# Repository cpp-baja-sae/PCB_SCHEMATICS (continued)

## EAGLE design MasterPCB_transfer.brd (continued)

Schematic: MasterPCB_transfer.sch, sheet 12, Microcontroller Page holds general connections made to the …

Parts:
40G_GPIO: SMALL_TP
!CS_ADC: SMALL_TP
!IMU_CS: SMALL_TP
!IMU_RST: SMALL_TP
!ISO_CS: SMALL_TP
!TEMP_CS: SMALL_TP
BUSY_ADC_1, BUSY_ADC_2, BUSY_ADC_3: SMALL_TP
CD/DAT3_SPI-CS: SMALL_TP
CLK: SMALL_TP
CMD_SPI-DI: SMALL_TP
CONVAB_ADC: SMALL_TP
DAT1, DAT2: SMALL_TP
DAT_SPI-DO: SMALL_TP
DIN1, DIN2, DIN3, DIN4, DIN5, DIN6, DIN7, DIN8: SMALL_TP
DOUTA_ADC_1, DOUTA_ADC_2, DOUTA_ADC_3: SMALL_TP
DOUTB_ADC_1, DOUTB_ADC_2, DOUTB_ADC_3: SMALL_TP
FSTD_ADC_1, FSTD_ADC_2, FSTD_ADC_3: SMALL_TP
GPS_EN: SMALL_TP
GPS_RX: SMALL_TP
GPS_TX: SMALL_TP
IMU_DIN: SMALL_TP
IMU_DOUT: SMALL_TP
IMU_DR: SMALL_TP
IMU_SCLK: SMALL_TP
IMU_SYNC: SMALL_TP
ISO_MISO: SMALL_TP
ISO_MOSI: SMALL_TP
ISO_SPI_CH_SEL: SMALL_TP
ISO_SPI_HZ_SW: SMALL_TP
ISO_SPI_SCLK: SMALL_TP
ISO_SPI_SLOW: SMALL_TP
J4, J12, J14: TFM-140-02-L-D-WT-K; SAMTEC_TFM-140-02-L-D-WT-K
LED_1, LED_2, LED_3: SMALL_TP
LED_P: SMALL_TP
MASS_ON: SMALL_TP
OS0_ADC, OS1_ADC, OS2_ADC: SMALL_TP
PA0, PA3, PA4, PA5, PA6, PA8, PA9, PA10, PA11, PA12, PA13, PA14, PA15: SMALL_TP
PB0, PB1, PB2, PB3, PB4, PB5, PB6, PB7, PB8, PB9, PB10, PB11, PB12, PB14, PB15: SMALL_TP
PC0, PC2, PC3, PC6, PC7, PC8, PC9, PC10, PC11, PC12, PC13: SMALL_TP
PD0, PD1, PD2, PD3, PD4, PD5, PD6, PD7, PD11, PD12, PD13, PD14, PD15: SMALL_TP
PE0, PE1, PE2, PE3, PE4, PE5, PE6, PE7, PE8, PE9, PE10, PE11, PE12, PE13, PE14, PE15: SMALL_TP
PF0, PF1, PF2, PF3, PF4, PF5, PF6, PF7, PF8, PF9, PF10, PF11, PF12, PF13, PF14, PF15: SMALL_TP
PG0, PG1, PG2, PG3, PG4, PG5, PG6, PG8, PG9, PG10, PG12, PG14, PG15: SMALL_TP
PH1: SMALL_TP
P_FAULT1, P_FAULT2, P_FAULT3: SMALL_TP
RST_ADC: SMALL_TP
SCL1, SCL2: SMALL_TP
SCLK_ADC: SMALL_TP
SDA1, SDA2: SMALL_TP
TEMP_MISO: SMALL_TP
TEMP_SCLK: SMALL_TP
U$5, U$7, U$9, U$10, U$14, U$15: THROUGH_HOLE; 1/16TH_BOLT
UC1: NUCLEO_H723ZG

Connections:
3.3V_MCU: UC1.3V3_VDD
3.3V_SWITCHING: J12.28, J12.30, J12.32, J12.34, J12.36, J12.38; also elsewhere on the board
5V_CONNECTOR: J12.16, J12.18, J12.20, J12.22, J12.24, J12.26; also elsewhere on the board
5V_MCU: UC1.5V_EXT; also elsewhere on the board
13.5V_BUS: J12.02, J12.04, J12.06, J12.08, J12.10, J12.12, J12.14; also elsewhere on the board
40G_GPIO: 40G_GPIO.TP, J4.40; also elsewhere on the board
!CS_ADC: !CS_ADC.TP, J4.53; also elsewhere on the board
!IMU_CS: !IMU_CS.TP, J4.03; also elsewhere on the board
!IMU_RST: !IMU_RST.TP, J4.01; also elsewhere on the board
!ISO_CS: !ISO_CS.TP, J4.28; also elsewhere on the board
!THERMOCOUPLE_CS: !TEMP_CS.TP, J4.36; also elsewhere on the board
BUSY_ADC_1: BUSY_ADC_1.TP, J4.55; also elsewhere on the board
BUSY_ADC_2: BUSY_ADC_2.TP, J4.63; also elsewhere on the board
BUSY_ADC_3: BUSY_ADC_3.TP, J4.71; also elsewhere on the board
CONVSTAB_ADC: CONVAB_ADC.TP, J4.47; also elsewhere on the board
DOUTA_ADC_1: DOUTA_ADC_1.TP, J4.61; also elsewhere on the board
DOUTA_ADC_2: DOUTA_ADC_2.TP, J4.69; also elsewhere on the board
DOUTA_ADC_3: DOUTA_ADC_3.TP, J4.77; also elsewhere on the board
DOUTB_ADC_1: DOUTB_ADC_1.TP, J4.59; also elsewhere on the board
DOUTB_ADC_2: DOUTB_ADC_2.TP, J4.67; also elsewhere on the board
DOUTB_ADC_3: DOUTB_ADC_3.TP, J4.75; also elsewhere on the board
D_SENSE1: DIN1.TP, J4.66; also elsewhere on the board
D_SENSE2: DIN2.TP, J4.68; also elsewhere on the board
D_SENSE3: DIN3.TP, J4.70; also elsewhere on the board
D_SENSE4: DIN4.TP, J4.72; also elsewhere on the board
D_SENSE5: DIN5.TP, J4.74; also elsewhere on the board
D_SENSE6: DIN6.TP, J4.76; also elsewhere on the board
D_SENSE7: DIN7.TP, J4.78; also elsewhere on the board
D_SENSE8: DIN8.TP, J4.80; also elsewhere on the board
ETH_CRS_DV: UC1.PA7
ETH_MDC: UC1.PC1
ETH_MDIO: UC1.PA2
ETH_REF_CLK: UC1.PA1
ETH_RXD0: UC1.PC4
ETH_RXD1: UC1.PC5
ETH_TXD0: UC1.PG13
ETH_TXD1: UC1.PB13
ETH_TX_EN: UC1.PG11
FIRSTDATA_ADC_1: FSTD_ADC_1.TP, J4.57; also elsewhere on the board
FIRSTDATA_ADC_2: FSTD_ADC_2.TP, J4.65; also elsewhere on the board
FIRSTDATA_ADC_3: FSTD_ADC_3.TP, J4.73; also elsewhere on the board
FLASH_CD/DAT3_SPI-CS: CD/DAT3_SPI-CS.TP, J4.08; also elsewhere on the board
FLASH_CLK: CLK.TP, J4.12; also elsewhere on the board
FLASH_CMD_SPI-DI: CMD_SPI-DI.TP, J4.10; also elsewhere on the board
FLASH_DAT0_SPI-DO: DAT_SPI-DO.TP, J4.02; also elsewhere on the board
FLASH_DAT1: DAT1.TP, J4.04; also elsewhere on the board
FLASH_DAT2: DAT2.TP, J4.06; also elsewhere on the board
GND: J12.39, J12.40, J12.41, J12.42, J12.43, J12.44, J12.45, J12.46, J12.47, J12.48, J12.49, J12.50, J12.51, J12.52, J12.53, J12.54, J12.55, J12.56, J12.57, J12.58, J12.59, J12.60, J12.61, J12.62, J12.63, J12.64, J12.65, J12.66, J12.67, J12.68, J12.69, J12.70, J12.71, J12.72, J12.73, J12.74, J12.75, J12.76, J12.77, J12.78, J12.79, J12.80, UC1.10 (GND), UC1.19 (GND), UC1.40 (GND), UC1.53 (GND), UC1.64 (GND), UC1.71 (GND), UC1.72 (GND), UC1.79 (GND), UC1.91 (GND), UC1.92 (GND), UC1.93 (GND), UC1.122 (GND), UC1.131 (GND), UC1.143 (GND), UC1.144 (GND); also elsewhere on the board
GPS_EN: GPS_EN.TP, J4.39; also elsewhere on the board
GPS_RX: GPS_RX.TP, J4.37; also elsewhere on the board
GPS_TX: GPS_TX.TP, J4.35; also elsewhere on the board
IMU_DIN: IMU_DIN.TP, J4.05; also elsewhere on the board
IMU_DOUT: IMU_DOUT.TP, J4.07; also elsewhere on the board
IMU_DR: IMU_DR.TP, J4.13; also elsewhere on the board
IMU_SCLK: IMU_SCLK.TP, J4.09; also elsewhere on the board
IMU_SYNC: IMU_SYNC.TP, J4.11; also elsewhere on the board
ISO_MISO: ISO_MISO.TP, J4.26; also elsewhere on the board
ISO_MOSI: ISO_MOSI.TP, J4.24; also elsewhere on the board
ISO_SPI_CH_SEL: ISO_SPI_CH_SEL.TP, J4.18; also elsewhere on the board
ISO_SPI_HIGH_Z_SWITCH: ISO_SPI_HZ_SW.TP, J4.20; also elsewhere on the board
ISO_SPI_SCLK: ISO_SPI_SCLK.TP, J4.22; also elsewhere on the board
ISO_SPI_SLOW: ISO_SPI_SLOW.TP, J4.30; also elsewhere on the board
LED_OUT1: J4.62, LED_1.TP; also elsewhere on the board
LED_OUT2: J4.60, LED_2.TP; also elsewhere on the board
LED_OUT3: J4.58, LED_3.TP; also elsewhere on the board
MASS_ON: J4.25, MASS_ON.TP; also elsewhere on the board
OS0_ADC: J4.41, OS0_ADC.TP; also elsewhere on the board
OS1_ADC: J4.43, OS1_ADC.TP; also elsewhere on the board
OS2_ADC: J4.45, OS2_ADC.TP; also elsewhere on the board
PA0: J14.01, PA0.TP, UC1.PA0
PA3: J14.03, PA3.TP, UC1.PA3
PA4: J14.05, PA4.TP, UC1.PA4
PA5: J14.07, PA5.TP, UC1.PA5
PA6: J14.09, PA6.TP, UC1.PA6
PA8: J14.11, PA8.TP, UC1.PA8
PA9: J14.13, PA9.TP, UC1.PA9
PA10: J14.15, PA10.TP, UC1.PA10
PA11: J14.17, PA11.TP, UC1.PA11
PA12: J14.19, PA12.TP, UC1.PA12
PA13: J14.21, PA13.TP, UC1.PA13
PA14: J14.23, PA14.TP, UC1.PA14
PA15: J14.25, PA15.TP, UC1.PA15
PB0: J14.27, PB0.TP, UC1.PB0
PB1: J14.29, PB1.TP, UC1.PB1
PB2: J14.31, PB2.TP, UC1.PB2
PB3: J14.33, PB3.TP, UC1.PB3
PB4: J14.35, PB4.TP, UC1.PB4
PB5: J14.37, PB5.TP, UC1.PB5
PB6: J14.39, PB6.TP, UC1.PB6
PB7: J14.79, PB7.TP, UC1.PB7
PB8: J14.77, PB8.TP, UC1.PB8
PB9: J14.75, PB9.TP, UC1.PB9
PB10: J14.73, PB10.TP, UC1.PB10
PB11: J14.71, PB11.TP, UC1.PB11
PB12: J14.69, PB12.TP, UC1.PB12
PB14: J14.65, PB14.TP, UC1.PB14
PB15: J14.63, PB15.TP, UC1.PB15
PC0: J14.61, PC0.TP, UC1.PC0
PC2: J14.59, PC2.TP, UC1.PC2
PC3: J14.57, PC3.TP, UC1.PC3
PC6: J14.55, PC6.TP, UC1.PC6
PC7: J14.53, PC7.TP, UC1.PC7
PC8: J14.51, PC8.TP, UC1.PC8
PC9: J14.49, PC9.TP, UC1.PC9
PC10: J14.47, PC10.TP, UC1.PC10
PC11: J14.45, PC11.TP, UC1.PC11
PC12: J14.43, PC12.TP, UC1.PC12
PC13: J14.41, PC13.TP, UC1.PC13
PC14-0SC32_IN: UC1.PC14
PC15-OSC32_OUT: UC1.PC15
PD0: J14.02, PD0.TP, UC1.PD0
PD1: J14.04, PD1.TP, UC1.PD1
PD2: J14.06, PD2.TP, UC1.PD2
PD3: J14.08, PD3.TP, UC1.PD3
PD4: J14.10, PD4.TP, UC1.PD4
PD5: J14.12, PD5.TP, UC1.PD5
PD6: J14.14, PD6.TP, UC1.PD6
PD7: J14.16, PD7.TP, UC1.PD7
PD11: J14.18, PD11.TP, UC1.PD11
PD12: J14.20, PD12.TP, UC1.PD12
PD13: J14.22, PD13.TP, UC1.PD13
PD14: J14.24, PD14.TP, UC1.PD14
PD15: J14.26, PD15.TP, UC1.PD15
PE0: J14.28, PE0.TP, UC1.PE0
PE1: J14.30, PE1.TP, UC1.PE1
PE2: J14.32, PE2.TP, UC1.PE2
PE3: J14.34, PE3.TP, UC1.PE3
PE4: J14.36, PE4.TP, UC1.PE4
PE5: J14.38, PE5.TP, UC1.PE5
PE6: J14.40, PE6.TP, UC1.PE6
PE7: J14.80, PE7.TP, UC1.PE7
PE8: J14.78, PE8.TP, UC1.PE8
PE9: J14.76, PE9.TP, UC1.PE9
PE10: J14.74, PE10.TP, UC1.PE10
PE11: J14.72, PE11.TP, UC1.PE11
PE12: J14.70, PE12.TP, UC1.PE12
PE13: J14.68, PE13.TP, UC1.PE13
PE14: J14.66, PE14.TP, UC1.PE14
PE15: J14.64, PE15.TP, UC1.PE15
PF0: J12.23, PF0.TP, UC1.PF0
PF1: J14.62, PF1.TP, UC1.PF1
PF2: J14.60, PF2.TP, UC1.PF2
PF3: J14.58, PF3.TP, UC1.PF3
PF4: J14.56, PF4.TP, UC1.PF4
PF5: J14.54, PF5.TP, UC1.PF5
PF6: J14.52, PF6.TP, UC1.PF6
PF7: J14.50, PF7.TP, UC1.PF7
PF8: J14.48, PF8.TP, UC1.PF8
PF9: J14.46, PF9.TP, UC1.PF9
PF10: J14.44, PF10.TP, UC1.PF10
PF11: J14.42, PF11.TP, UC1.PF11
PF12: J12.01, PF12.TP, UC1.PF12
PF13: J12.03, PF13.TP, UC1.PF13
PF14: J12.05, PF14.TP, UC1.PF14
PF15: J12.07, PF15.TP, UC1.PF15
PG0: J12.09, PG0.TP, UC1.PG0
PG1: J12.11, PG1.TP, UC1.PG1
PG2: J12.13, PG2.TP, UC1.PG2
PG3: J12.15, PG3.TP, UC1.PG3
PG4: J12.17, PG4.TP, UC1.PG4
PG5: J12.19, PG5.TP, UC1.PG5
PG6: J12.21, PG6.TP, UC1.PG6
PG8: J12.25, PG8.TP, UC1.PG8
PG9: J12.27, PG9.TP, UC1.PG9
PG10: J12.29, PG10.TP, UC1.PG10
PG12: J12.31, PG12.TP, UC1.PG12
PG14: J12.33, PG14.TP, UC1.PG14
PG15: J12.35, PG15.TP, UC1.PG15
PH0-OSC_IN: UC1.PH0
PH1: J12.37, PH1.TP, UC1.PH1
POWER_FAULT1: J4.15, P_FAULT1.TP; also elsewhere on the board
POWER_FAULT2: J4.17, P_FAULT2.TP; also elsewhere on the board
POWER_FAULT3: J4.19, P_FAULT3.TP; also elsewhere on the board
P_LED: J4.64, LED_P.TP; also elsewhere on the board
RESET_ADC: J4.49, RST_ADC.TP; also elsewhere on the board
SCL1: J4.23, SCL1.TP; also elsewhere on the board
SCL2: J4.29, SCL2.TP; also elsewhere on the board
SCLK_ADC: J4.51, SCLK_ADC.TP; also elsewhere on the board
SDA1: J4.21, SDA1.TP; also elsewhere on the board
SDA2: J4.27, SDA2.TP; also elsewhere on the board
THERMOCOUPLE_MISO: J4.34, TEMP_MISO.TP; also elsewhere on the board
THERMOCOUPLE_SCLK: J4.32, TEMP_SCLK.TP; also elsewhere on the board
USART3_TX: UC1.PD8
USART4_RX: UC1.PD9
USB_FS_OVCR: UC1.PG7
USB_FS_PWR_EN: UC1.PD10

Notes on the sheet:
Pins labeled DNC _ # are pins connected for hardware on board
RED LED - There is an issue YELLOW LED - Digital coms GREEN LED - Power Good BLUE LED - Power at location is available
Board LED indicators
Microcontroller pin breakout connector Expose all non-static set pins for easy access and to enable swapping pin configurations as well
All digital connections go through connector Enables easy flexibility to rewire any digital system on demand
Flash interface
ISO SPI link interface
Back up thermocouple spi link interface
Digital input
Driver indicators
GPS interface
IMU interface
Power fault input
E-Fuse interface
ADC interface

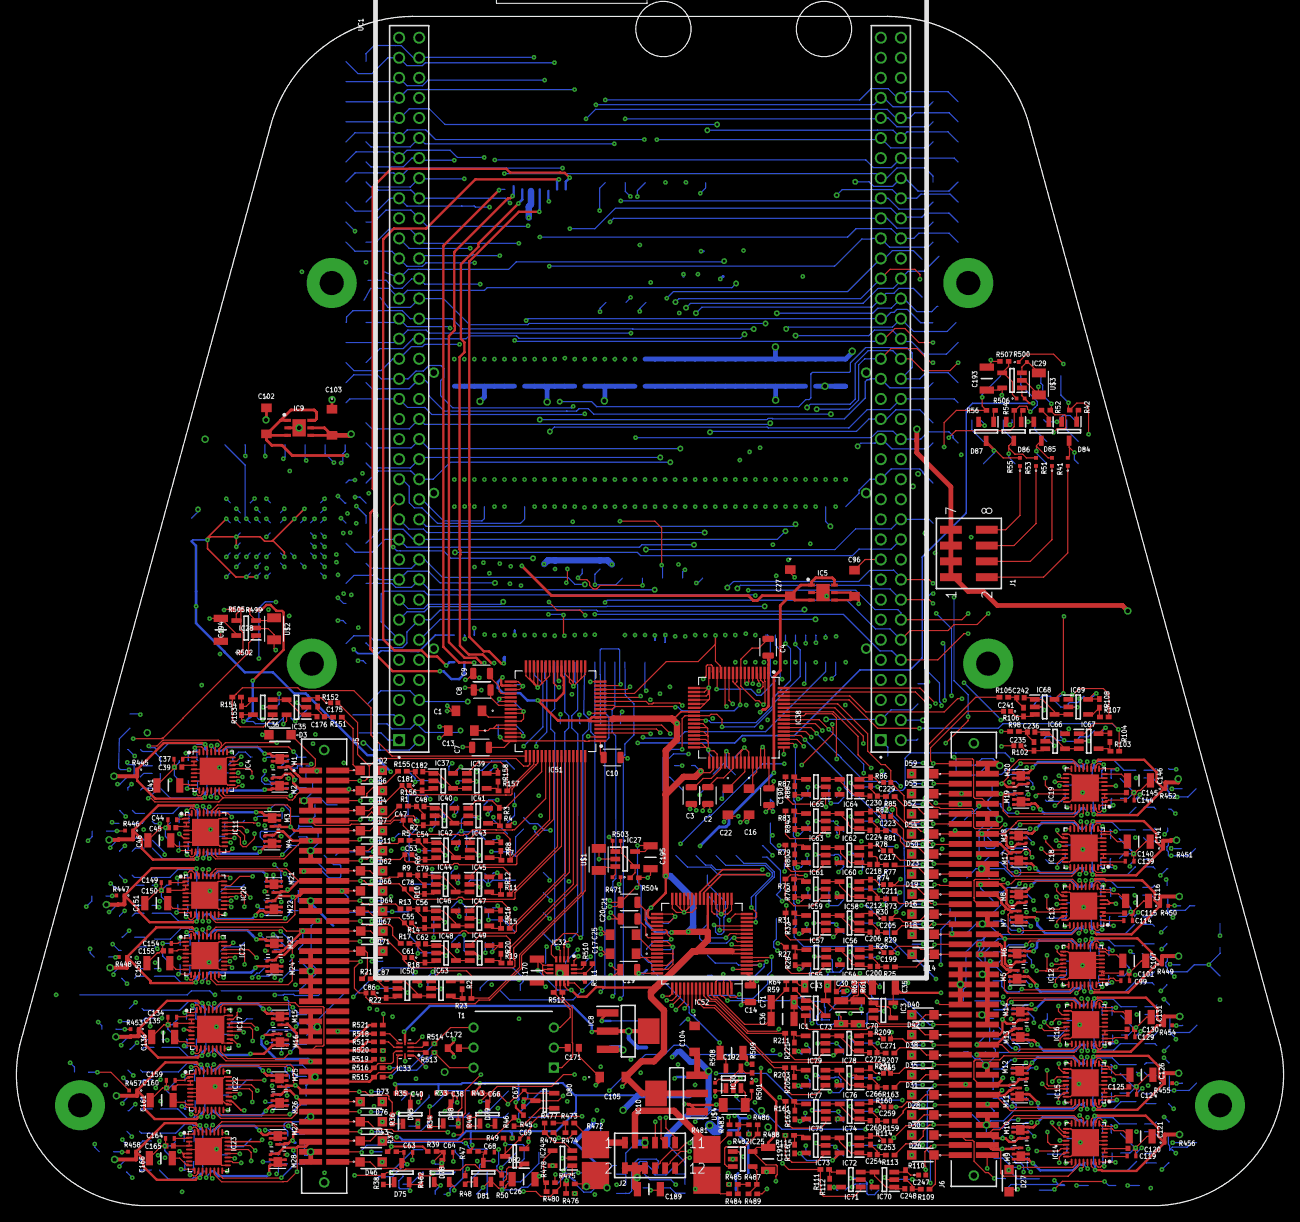
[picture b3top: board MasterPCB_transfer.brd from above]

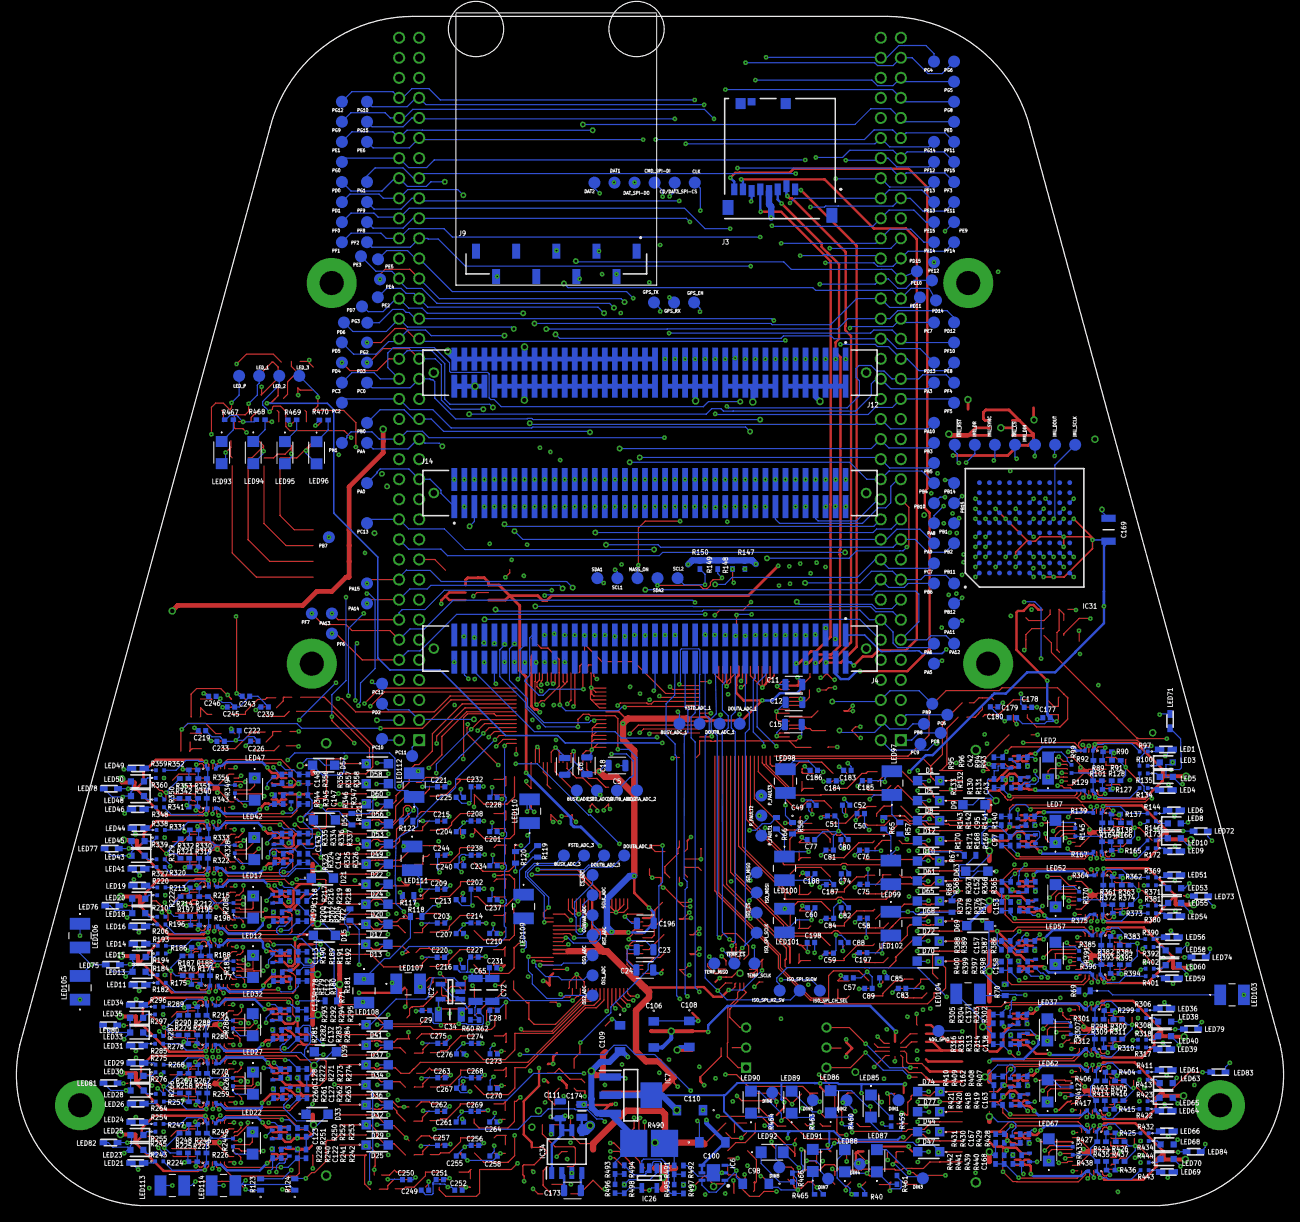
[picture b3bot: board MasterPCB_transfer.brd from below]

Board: 6 copper layers, 160.4 x 150.5 mm, 1268 parts (804 on the bottom side), 863 nets.

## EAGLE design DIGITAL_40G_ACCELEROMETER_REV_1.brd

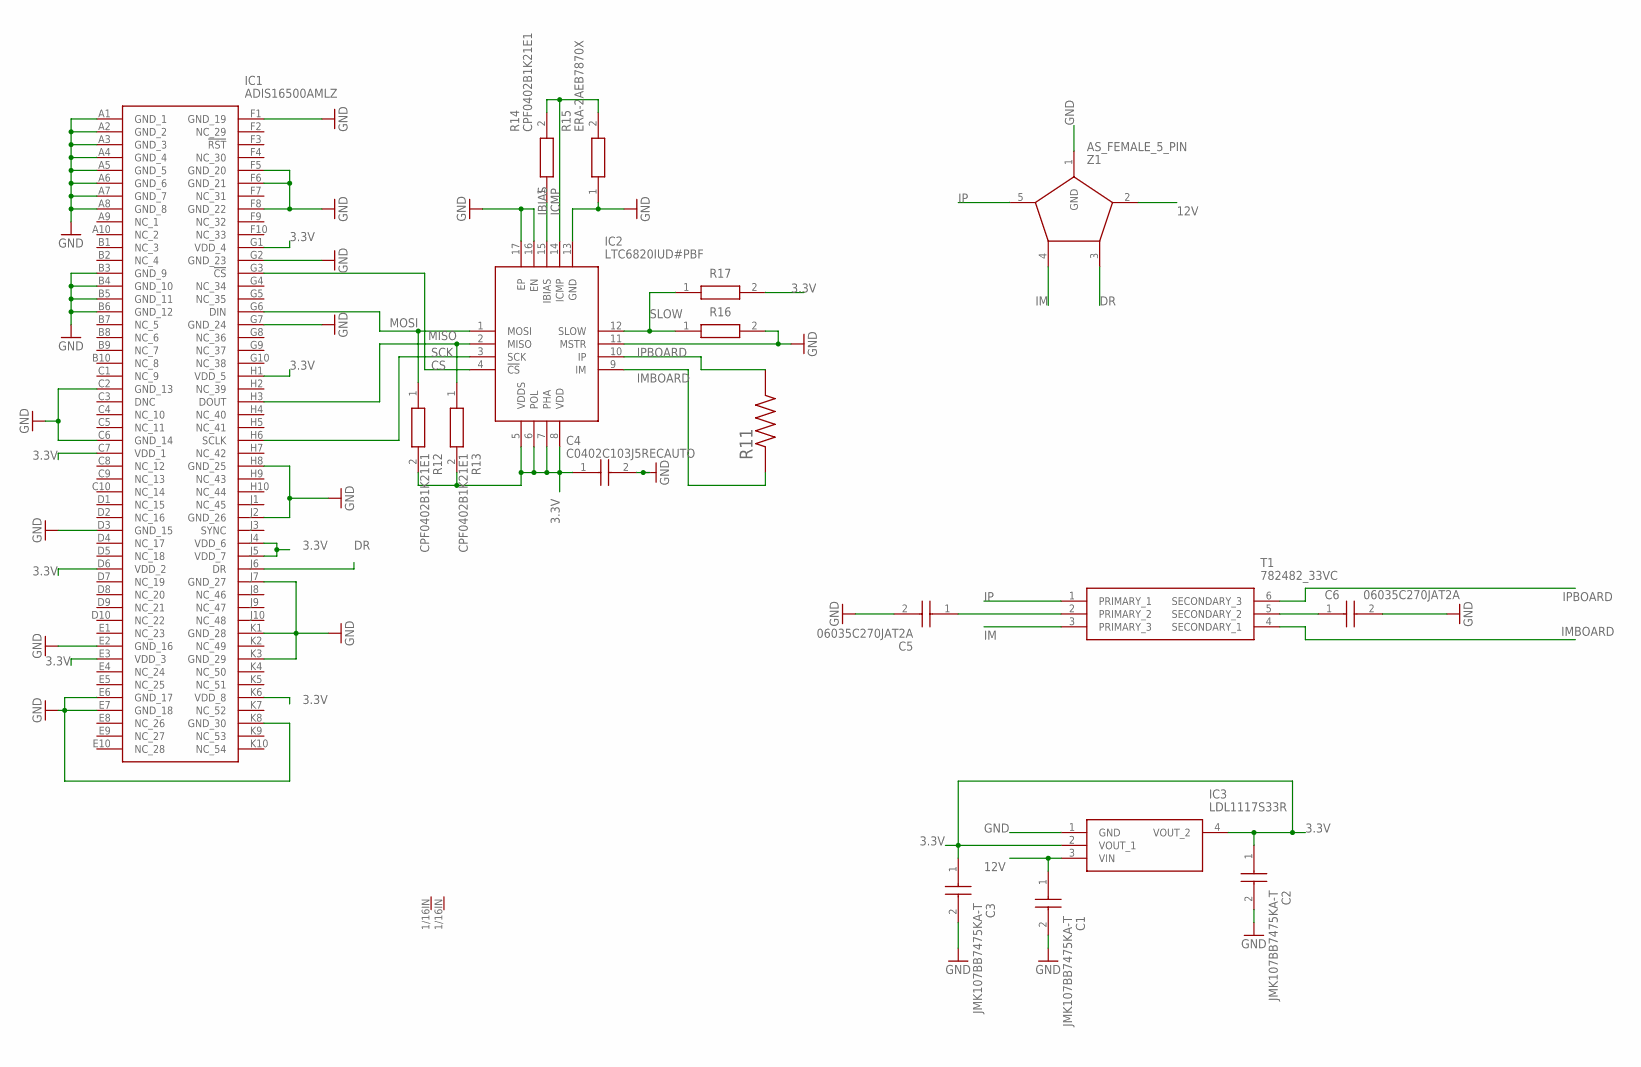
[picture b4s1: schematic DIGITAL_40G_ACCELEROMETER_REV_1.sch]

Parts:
C1, C2, C3: JMK107BB7475KA-T; CAPC1608X90N
C4: C0402C103J5RECAUTO; CAPC1005X55N
C5, C6: 06035C270JAT2A; CAPC1608X90N
IC1: ADIS16500AMLZ; BGA100C127P10X10_1500X1500X608
IC2: LTC6820IUD#PBF; QFN50P300X300X80-17N
IC3: LDL1117S33R; SOT230P700X180-4N
R11: 100; RESC1005X40N
R12, R13, R14: CPF0402B1K21E1; RESC1005X35N
R15: ERA-2AEB7870X; ERA2AED122X
R16, R17: CRG0402ZR; RESC1005X40N
T1: 782482_33VC; DIP1016W60P254L914H635Q6N
U$3, U$4: THROUGH_HOLE; 1/16TH_BOLT
Z1: AS_FEMALE_5_PIN

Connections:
3.3V: C2.1, C3.1, C4.1, IC1.C7 (VDD_1), IC1.D6 (VDD_2), IC1.E3 (VDD_3), IC1.G1 (VDD_4), IC1.H1 (VDD_5), IC1.J4 (VDD_6), IC1.J5 (VDD_7), IC1.K6 (VDD_8), IC2.5 (VDDS), IC2.6 (POL), IC2.7 (PHA), IC2.8 (VDD), IC3.2 (VOUT_1), IC3.4 (VOUT_2), R12.2, R13.2, R17.2
12V: C1.1, IC3.3 (VIN), Z1.2 (1)
CS: IC1.G3 (!CS), IC2.4 (!CS)
DR: IC1.J6 (DR), Z1.3 (2)
GND: C1.2, C2.2, C3.2, C4.2, C5.2, C6.2, IC1.A1 (GND_1), IC1.A2 (GND_2), IC1.A3 (GND_3), IC1.A4 (GND_4), IC1.A5 (GND_5), IC1.A6 (GND_6), IC1.A7 (GND_7), IC1.A8 (GND_8), IC1.B3 (GND_9), IC1.B4 (GND_10), IC1.B5 (GND_11), IC1.B6 (GND_12), IC1.C2 (GND_13), IC1.C6 (GND_14), IC1.D3 (GND_15), IC1.E2 (GND_16), IC1.E6 (GND_17), IC1.E7 (GND_18), IC1.F1 (GND_19), IC1.F5 (GND_20), IC1.F6 (GND_21), IC1.F8 (GND_22), IC1.G2 (GND_23), IC1.G7 (GND_24), IC1.H8 (GND_25), IC1.J2 (GND_26), IC1.J7 (GND_27), IC1.K1 (GND_28), IC1.K3 (GND_29), IC1.K8 (GND_30), IC2.11 (MSTR), IC2.13 (GND), IC2.16 (EN), IC2.17 (EP), IC3.1 (GND), R15.1, R16.2, Z1.1 (GND)
IBIAS: IC2.15 (IBIAS), R14.1
ICMP: IC2.14 (ICMP), R14.2, R15.2
IM: T1.3 (PRIMARY_3), Z1.4 (3)
IMBOARD: IC2.9 (IM), R11.1, T1.4 (SECONDARY_1)
IP: T1.1 (PRIMARY_1), Z1.5 (4)
IPBOARD: IC2.10 (IP), R11.2, T1.6 (SECONDARY_3)
MISO: IC1.H3 (DOUT), IC2.2 (MISO), R13.1
MOSI: IC1.G6 (DIN), IC2.1 (MOSI), R12.1
unnamed: C6.1, T1.5 (SECONDARY_2)
unnamed: C5.1, T1.2 (PRIMARY_2)
SCK: IC1.H6 (SCLK), IC2.3 (SCK)
SLOW: IC2.12 (SLOW), R16.1, R17.1

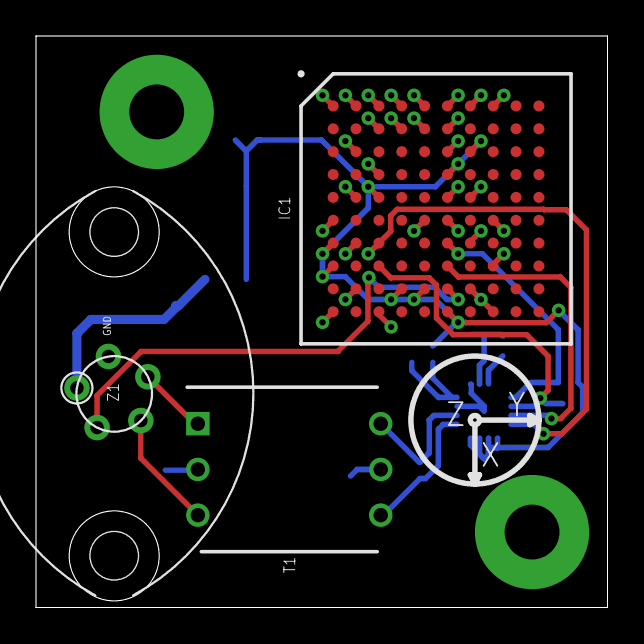
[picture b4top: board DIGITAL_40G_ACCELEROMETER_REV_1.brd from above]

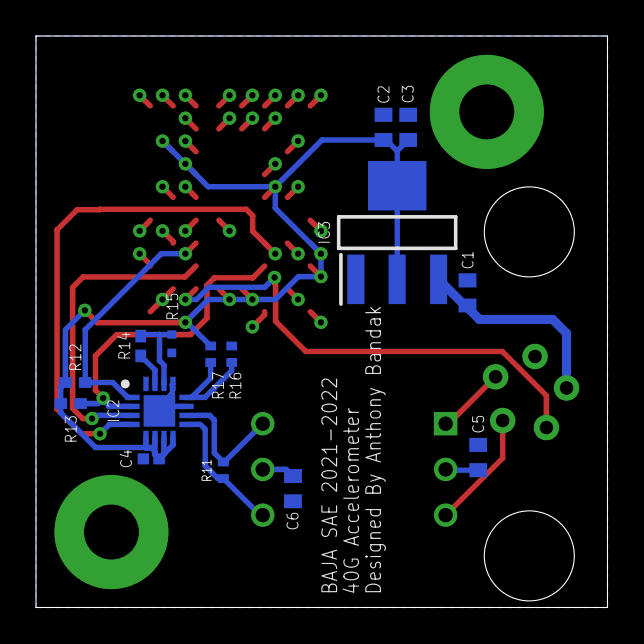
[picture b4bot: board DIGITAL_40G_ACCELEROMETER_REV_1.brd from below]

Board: 2 copper layers, 31.8 x 31.8 mm, 20 parts (16 on the bottom side), 17 nets.

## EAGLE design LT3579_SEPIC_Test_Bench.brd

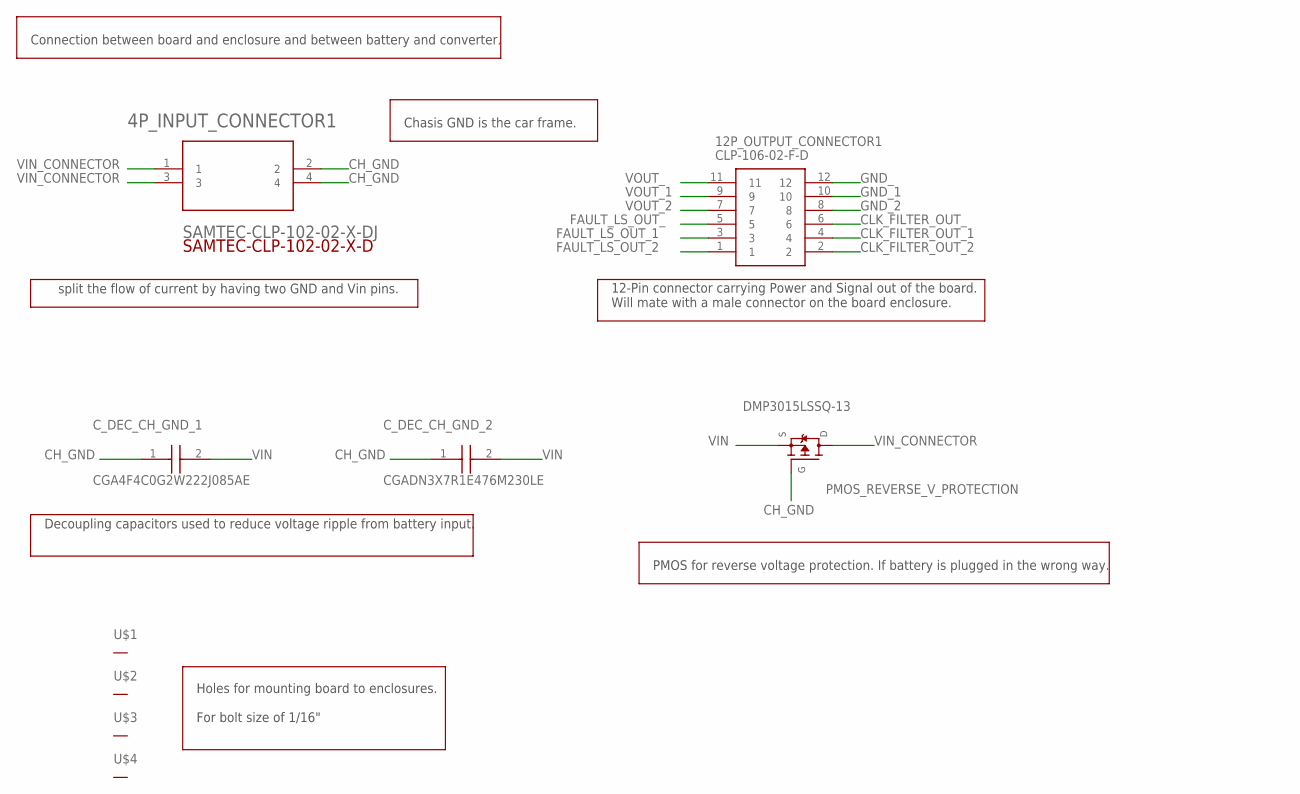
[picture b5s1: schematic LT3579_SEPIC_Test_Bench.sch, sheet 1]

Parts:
4P_INPUT_CONNECTOR1: SAMTEC-CLP-102-02-X-DJ; SAMTEC-CLP-102-02-X-D
12P_OUTPUT_CONNECTOR1: CLP-106-02-F-D; CLP-106-02-XXX
C_DEC_CH_GND_1: CGA4F4C0G2W222J085AE; CAPC2012X100N
C_DEC_CH_GND_2: CGADN3X7R1E476M230LE; CAPC7563X250N
PMOS_REVERSE_V_PROTECTION: DMP3015LSSQ-13; SOIC127P600X170-8N
U$1, U$2, U$3, U$4: THROUGH_HOLE_; THROUGH_HOLE

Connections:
CH_GND: 4P_INPUT_CONNECTOR1.2, 4P_INPUT_CONNECTOR1.4, C_DEC_CH_GND_1.1, C_DEC_CH_GND_2.1, PMOS_REVERSE_V_PROTECTION.4 (G1); also elsewhere on the board
CLK_FILTER_OUT_: 12P_OUTPUT_CONNECTOR1.6; also elsewhere on the board
CLK_FILTER_OUT_1: 12P_OUTPUT_CONNECTOR1.4; also elsewhere on the board
CLK_FILTER_OUT_2: 12P_OUTPUT_CONNECTOR1.2; also elsewhere on the board
FAULT_LS_OUT_: 12P_OUTPUT_CONNECTOR1.5; also elsewhere on the board
FAULT_LS_OUT_1: 12P_OUTPUT_CONNECTOR1.3; also elsewhere on the board
FAULT_LS_OUT_2: 12P_OUTPUT_CONNECTOR1.1; also elsewhere on the board
GND_: 12P_OUTPUT_CONNECTOR1.12; also elsewhere on the board
GND_1: 12P_OUTPUT_CONNECTOR1.10; also elsewhere on the board
GND_2: 12P_OUTPUT_CONNECTOR1.8; also elsewhere on the board
VIN: C_DEC_CH_GND_1.2, C_DEC_CH_GND_2.2, PMOS_REVERSE_V_PROTECTION.1 (S1), PMOS_REVERSE_V_PROTECTION.2 (S1), PMOS_REVERSE_V_PROTECTION.3 (S1); also elsewhere on the board
VIN_CONNECTOR: 4P_INPUT_CONNECTOR1.1, 4P_INPUT_CONNECTOR1.3, PMOS_REVERSE_V_PROTECTION.5 (D1), PMOS_REVERSE_V_PROTECTION.6 (D1), PMOS_REVERSE_V_PROTECTION.7 (D1), PMOS_REVERSE_V_PROTECTION.8 (D1)
VOUT_: 12P_OUTPUT_CONNECTOR1.11; also elsewhere on the board
VOUT_1: 12P_OUTPUT_CONNECTOR1.9; also elsewhere on the board
VOUT_2: 12P_OUTPUT_CONNECTOR1.7; also elsewhere on the board

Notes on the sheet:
Connection between board and enclosure and between battery and converter.
split the flow of current by having two GND and Vin pins.
12-Pin connector carrying Power and Signal out of the board. Will mate with a male connector on the board enclosure.
Decoupling capacitors used to reduce voltage ripple from battery input.
PMOS for reverse voltage protection. If battery is plugged in the wrong way.
Chasis GND is the car frame.
Holes for mounting board to enclosures. For bolt size of 1/16"

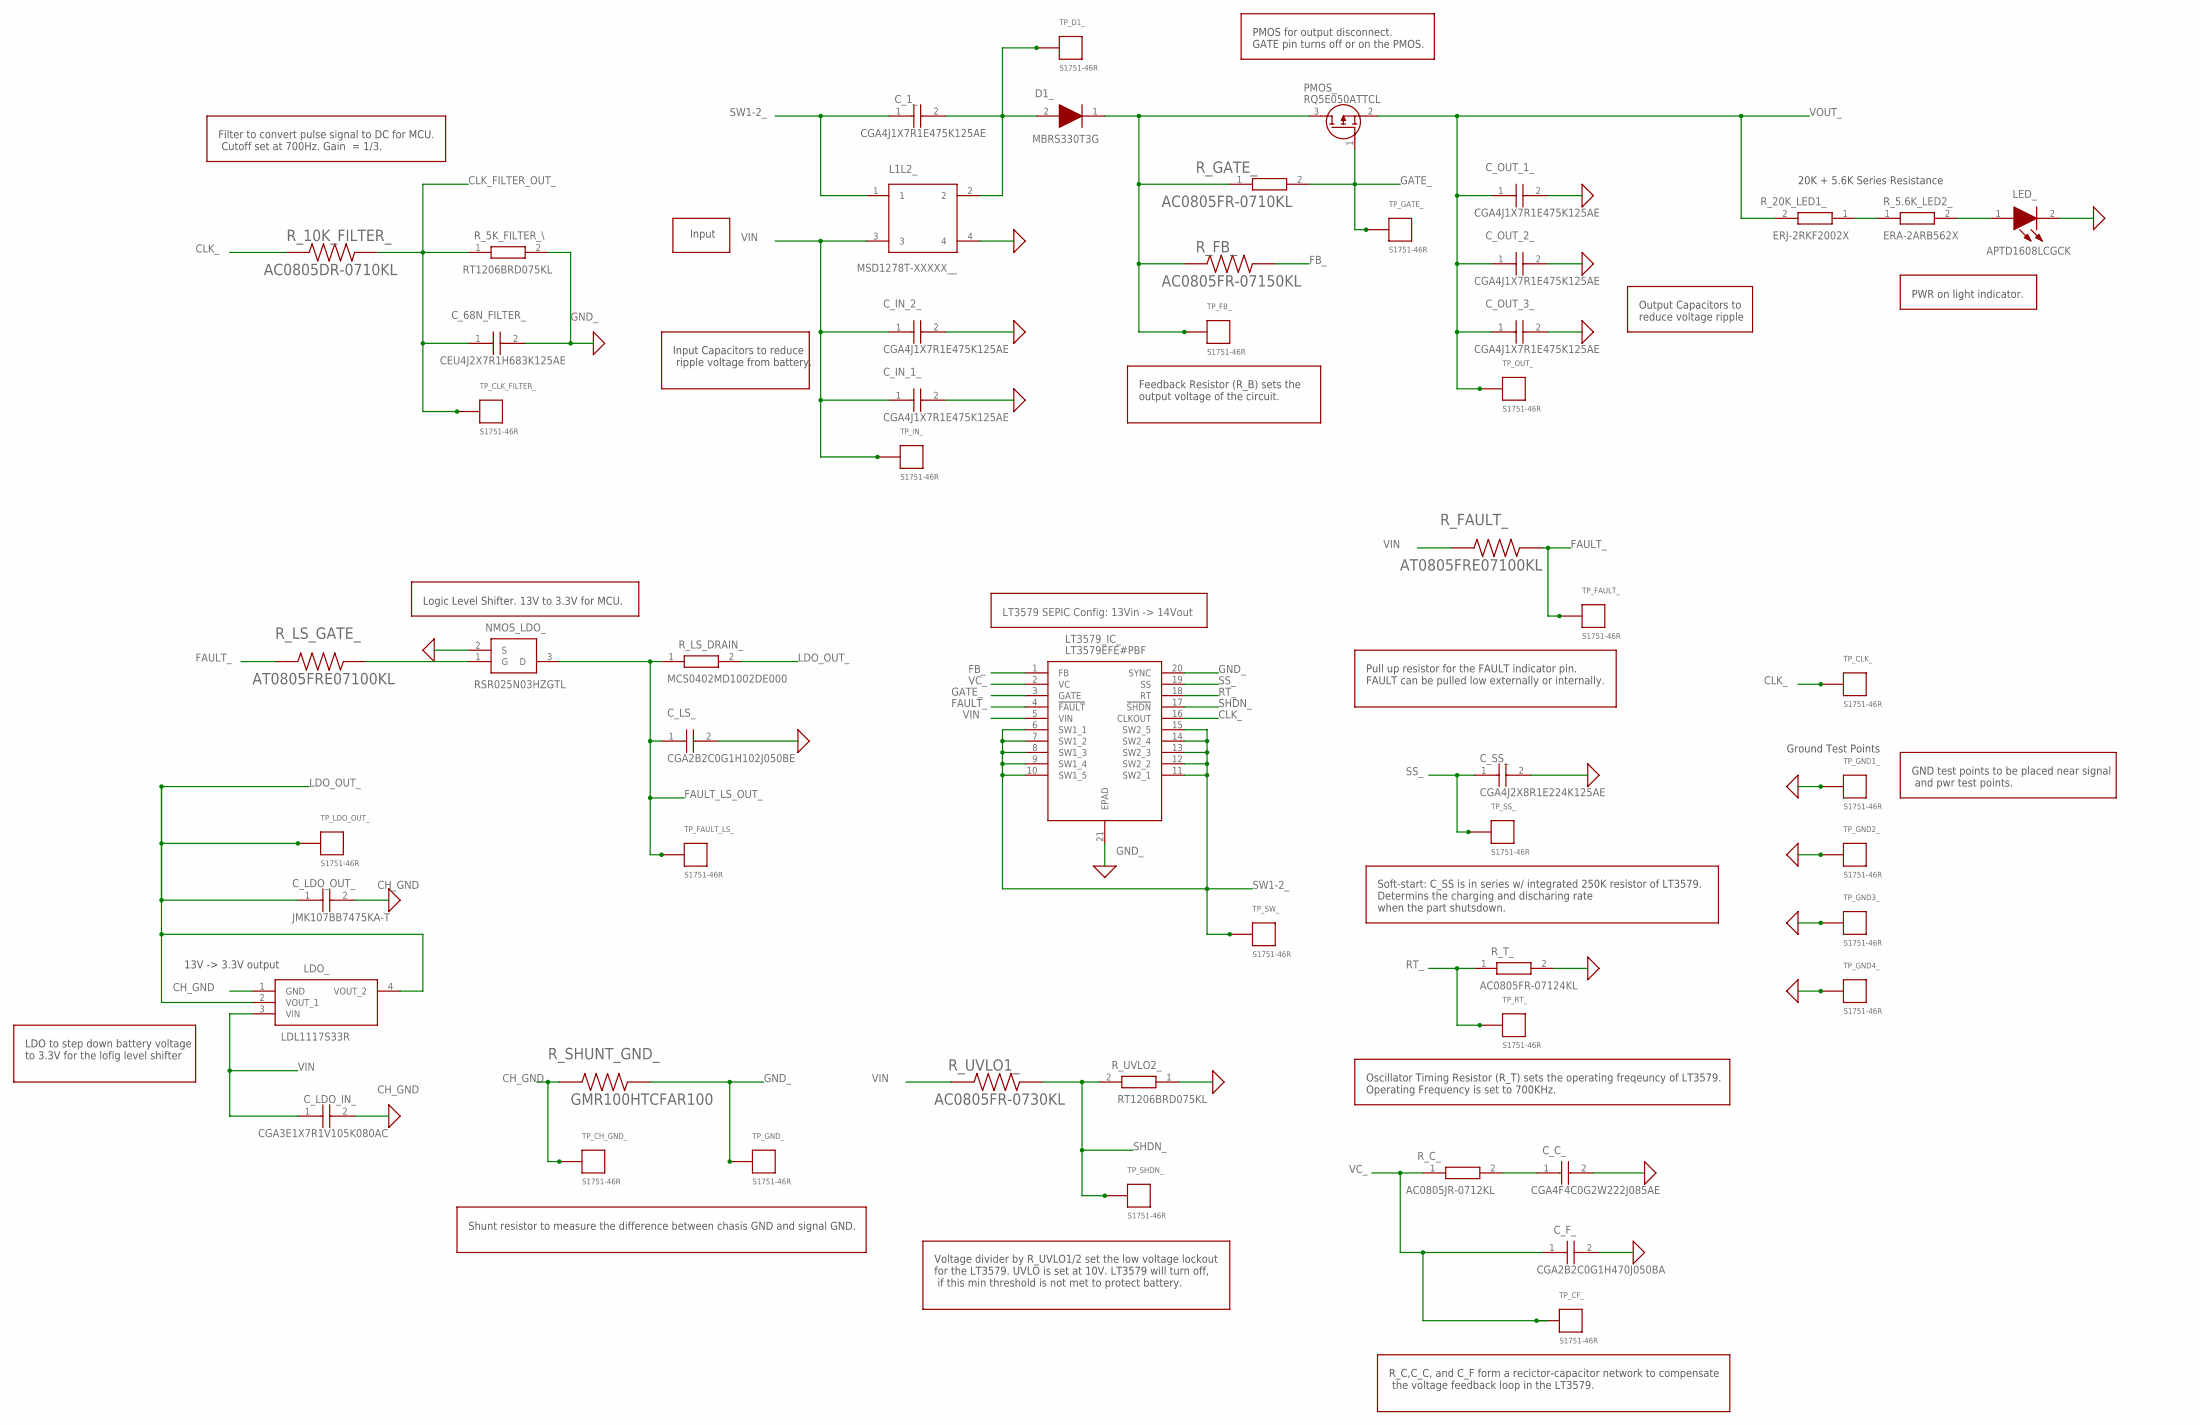
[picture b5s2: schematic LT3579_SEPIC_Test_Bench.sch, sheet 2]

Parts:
C_1_: CGA4J1X7R1E475K125AE; CAPC2012X145N
C_68N_FILTER_: CEU4J2X7R1H683K125AE; CAPC2013X150N
C_C_: CGA4F4C0G2W222J085AE; CAPC2012X100N
C_F_: CGA2B2C0G1H470J050BA; CAPC1005X55N
C_IN_1_, C_IN_2_: CGA4J1X7R1E475K125AE; CAPC2012X145N
C_LDO_IN_: CGA3E1X7R1V105K080AC; CAPC1608X90N
C_LDO_OUT_: JMK107BB7475KA-T; CAPC1608X90N
C_LS_: CGA2B2C0G1H102J050BE; CAPC1005X55N
C_OUT_1_, C_OUT_2_, C_OUT_3_: CGA4J1X7R1E475K125AE; CAPC2012X145N
C_SS_: CGA4J2X8R1E224K125AE; CAPC2012X145N
D1_: MBRS330T3G; DIOM7958X256N
L1L2_: MSD1278T-XXXXX__; MSD1278T-822MLXX
LDO_: LDL1117S33R; SOT230P700X180-4N
LED_: APTD1608LCGCK; APT1608CGCK
LT3579_IC_: LT3579EFE#PBF; SOP65P640X120-21N
NMOS_LDO_: RSR025N03HZGTL; SOT95P280X100-3N
PMOS_: RQ5E050ATTCL; SOT95P280X100-3N
R_5.6K_LED2_: ERA-2ARB562X; ERA2AED122X
R_5K_FILTER_\: RT1206BRD075KL; RESC3116X65N
R_10K_FILTER_: AC0805DR-0710KL; RESC2012X60N
R_20K_LED1_: ERJ-2RKF2002X; ERJ2R_(0402)
R_C_: AC0805JR-0712KL; RESC2012X60N
R_FAULT_: AT0805FRE07100KL; RESC2012X60N
R_FB_: AC0805FR-07150KL; RESC2012X60N
R_GATE_: AC0805FR-0710KL; RESC2012X60N
R_LS_DRAIN_: MCS0402MD1002DE000; RESC1005X37N
R_LS_GATE_: AT0805FRE07100KL; RESC2012X60N
R_SHUNT_GND_: GMR100HTCFAR100; RESC6432X55N
R_T_: AC0805FR-07124KL; RESC2012X60N
R_UVLO1_: AC0805FR-0730KL; RESC2012X60N
R_UVLO2_: RT1206BRD075KL; RESC3116X65N
TP_CF_: S1751-46R; S1751-46R_
TP_CH_GND_: S1751-46R; S1751-46R_
TP_CLK_: S1751-46R; S1751-46R_
TP_CLK_FILTER_: S1751-46R; S1751-46R_
TP_D1_: S1751-46R; S1751-46R_
TP_FAULT_: S1751-46R; S1751-46R_
TP_FAULT_LS_: S1751-46R; S1751-46R_
TP_FB_: S1751-46R; S1751-46R_
TP_GATE_: S1751-46R; S1751-46R_
TP_GND1_, TP_GND2_, TP_GND3_, TP_GND4_: S1751-46R; S1751-46R_
TP_GND_: S1751-46R; S1751-46R_
TP_IN_: S1751-46R; S1751-46R_
TP_LDO_OUT_: S1751-46R; S1751-46R_
TP_OUT_: S1751-46R; S1751-46R_
TP_RT_: S1751-46R; S1751-46R_
TP_SHDN_: S1751-46R; S1751-46R_
TP_SS_: S1751-46R; S1751-46R_
TP_SW_: S1751-46R; S1751-46R_

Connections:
CH_GND: C_LDO_IN_.2, C_LDO_OUT_.2, LDO_.1 (GND), R_SHUNT_GND_.1, TP_CH_GND_.1; also elsewhere on the board
CLK_: LT3579_IC_.16 (CLKOUT), R_10K_FILTER_.1, TP_CLK_.1; also elsewhere on the board
FAULT_: LT3579_IC_.4 (!FAULT), R_FAULT_.1, R_LS_GATE_.1, TP_FAULT_.1
FAULT_LS_OUT_: C_LS_.1, NMOS_LDO_.3 (D), R_LS_DRAIN_.1, TP_FAULT_LS_.1; also elsewhere on the board
FB_: LT3579_IC_.1 (FB), R_FB_.2
GATE_: LT3579_IC_.3 (GATE), PMOS_.1 (G), R_GATE_.2, TP_GATE_.1
GND_: C_68N_FILTER_.2, C_C_.2, C_F_.2, C_IN_1_.2, C_IN_2_.2, C_LS_.2, C_OUT_1_.2, C_OUT_2_.2, C_OUT_3_.2, C_SS_.2, L1L2_.4, LED_.2 (K), LT3579_IC_.20 (SYNC), LT3579_IC_.21 (EPAD), NMOS_LDO_.2 (S), R_5K_FILTER_\.2, R_SHUNT_GND_.2, R_T_.2, R_UVLO2_.1, TP_GND1_.1, TP_GND2_.1, TP_GND3_.1, TP_GND4_.1, TP_GND_.1; also elsewhere on the board
LDO_OUT_: C_LDO_OUT_.1, LDO_.2 (VOUT_1), LDO_.4 (VOUT_2), R_LS_DRAIN_.2, TP_LDO_OUT_.1; also elsewhere on the board
unnamed: C_C_.1, R_C_.2
unnamed: NMOS_LDO_.1 (G), R_LS_GATE_.2
unnamed: C_1_.2, D1_.2 (A), L1L2_.2, TP_D1_.1
unnamed: R_5.6K_LED2_.1, R_20K_LED1_.1
unnamed: D1_.1 (K), PMOS_.3 (D), R_FB_.1, R_GATE_.1, TP_FB_.1
unnamed: LED_.1 (A), R_5.6K_LED2_.2
unnamed: C_68N_FILTER_.1, R_5K_FILTER_\.1, R_10K_FILTER_.2, TP_CLK_FILTER_.1
RT_: LT3579_IC_.18 (RT), R_T_.1, TP_RT_.1
SHDN_: LT3579_IC_.17 (!SHDN), R_UVLO1_.1, R_UVLO2_.2, TP_SHDN_.1
SS_: C_SS_.1, LT3579_IC_.19 (SS), TP_SS_.1
SW1-2_: C_1_.1, L1L2_.1, LT3579_IC_.6 (SW1_1), LT3579_IC_.7 (SW1_2), LT3579_IC_.8 (SW1_3), LT3579_IC_.9 (SW1_4), LT3579_IC_.10 (SW1_5), LT3579_IC_.11 (SW2_1), LT3579_IC_.12 (SW2_2), LT3579_IC_.13 (SW2_3), LT3579_IC_.14 (SW2_4), LT3579_IC_.15 (SW2_5), TP_SW_.1
VC_: C_F_.1, LT3579_IC_.2 (VC), R_C_.1, TP_CF_.1
VIN: C_IN_1_.1, C_IN_2_.1, C_LDO_IN_.1, L1L2_.3, LDO_.3 (VIN), LT3579_IC_.5 (VIN), R_FAULT_.2, R_UVLO1_.2, TP_IN_.1; also elsewhere on the board
VOUT_: C_OUT_1_.1, C_OUT_2_.1, C_OUT_3_.1, PMOS_.2 (S), R_20K_LED1_.2, TP_OUT_.1; also elsewhere on the board

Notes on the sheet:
LT3579 SEPIC Config: 13Vin -> 14Vout
Ground Test Points
Filter to convert pulse signal to DC for MCU. Cutoff set at 700Hz. Gain = 1/3.
13V -> 3.3V output
Logic Level Shifter. 13V to 3.3V for MCU.
20K + 5.6K Series Resistance
PWR on light indicator.
Voltage divider by R_UVLO1/2 set the low voltage lockout for the LT3579. UVLO is set at 10V. LT3579 will turn off, if this min threshold is not met to protect battery.
Oscillator Timing Resistor (R_T) sets the operating freqeuncy of LT3579. Operating Frequency is set to 700KHz.
R_C,C_C, and C_F form a recictor-capacitor network to compensate the voltage feedback loop in the LT3579.
Soft-start: C_SS is in series w/ integrated 250K resistor of LT3579. Determins the charging and discharing rate when the part shutsdown.
Pull up resistor for the FAULT indicator pin. FAULT can be pulled low externally or internally.
Shunt resistor to measure the difference between chasis GND and signal GND.
LDO to step down battery voltage to 3.3V for the lofig level shifter
GND test points to be placed near signal and pwr test points.
Input Capacitors to reduce ripple voltage from battery.
Output Capacitors to reduce voltage ripple
PMOS for output disconnect. GATE pin turns off or on the PMOS.
Feedback Resistor (R_B) sets the output voltage of the circuit.
Input
